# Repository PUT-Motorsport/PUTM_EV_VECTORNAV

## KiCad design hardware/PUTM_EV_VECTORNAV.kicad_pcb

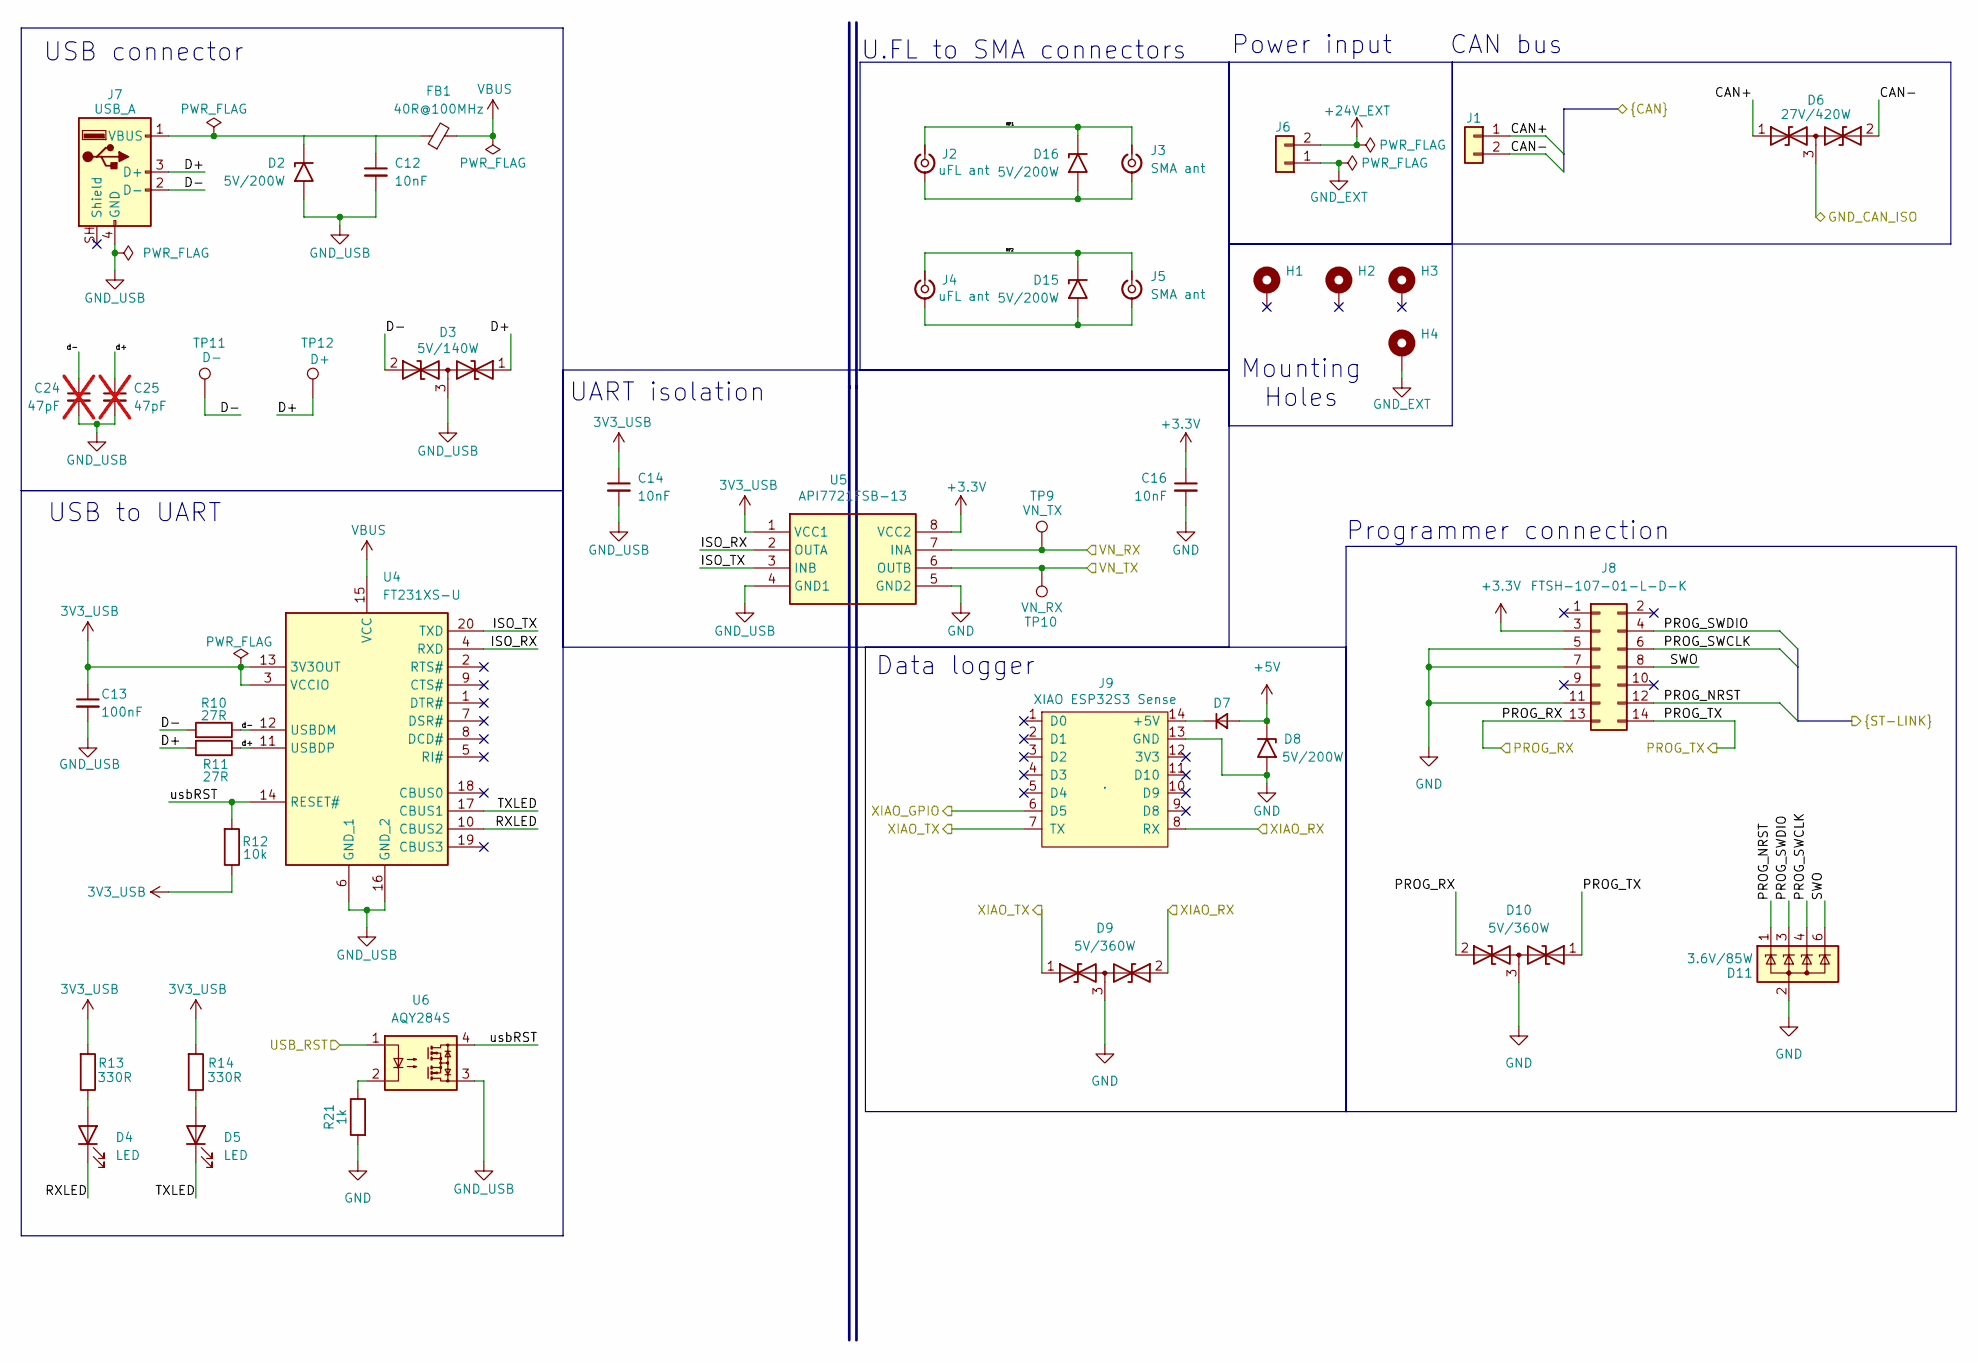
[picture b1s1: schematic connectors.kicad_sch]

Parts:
C12, C14, C16: 10nF; C_0603_1608Metric_Pad1.08x0.95mm_HandSolder
C13: 100nF; C_0603_1608Metric_Pad1.08x0.95mm_HandSolder; Mouser No 80-C0603C104M4RAUTO
C24, C25: 47pF; C_0603_1608Metric_Pad1.08x0.95mm_HandSolder; Mouser --; not fitted
D2, D8, D15, D16: 5V/200W; SODFL3618X110N
D3: 5V/140W; SOT-23-3
D4, D5: LED; D_0603_1608Metric_Pad1.05x0.95mm_HandSolder
D6: 27V/420W; SOT-23-3
D7: NSVRB751V40T1G; D_SOD-323_HandSoldering
D9, D10: 5V/360W; SOT-23_Handsoldering; Manufacturer_Part_Number STS232050B751; Mouser No 504-STS232050B751
D11: 3.6V/85W; SOT-23-6; Manufacturer_Part_Number ESDS304DBVR; Mouser No 595-ESDS304DBVR
FB1: 40R@100MHz; BEADC2012X110N
H1, H2, H3: MountingHole_Pad; MountingHole_3mm; Mouser ---
H4: MountingHole_Pad; MountingHole_3mm_Pad_Via; Mouser ---
J1, J6: Conn_01x02; StrainRelief; Manufacturer_Part_Number strain relief; Mouser ---
J2, J4: uFL ant; CONUFL001SMDT
J3, J5: SMA ant; SMACONNECTOR
J7: USB_A; UJ2AV4TH
J8: FTSH-107-01-L-D-K; FTSH-107-XX-YYY-D-K; Manufacturer_Part_Number FTSH-107-01-L-D-K; Mouser No 200-FTSH10701LDK
J9: XIAO ESP32S3 Sense; XIAO-ESP32S3-DIP; Mouser Part Number .
R10, R11: 27R; R_0603_1608Metric_Pad0.98x0.95mm_HandSolder
R12: 10k; R_0603_1608Metric_Pad0.98x0.95mm_HandSolder
R13, R14: 330R; R_0603_1608Metric_Pad0.98x0.95mm_HandSolder
R21: 1k; R_0603_1608Metric_Pad0.98x0.95mm_HandSolder
TP9: VN_TX; TestPoint_Pad_D1.0mm
TP10: VN_RX; TestPoint_Pad_D1.0mm
TP11: D-; TestPoint_Pad_D0.7mm
TP12: D+; TestPoint_Pad_D0.7mm
U4: FT231XS-U; SSOP-20_3.9x8.7mm_P0.635mm; Mouser Part Number 895-FT231XS-U
U5: API7721FSB-13; SOIC127P1150X280-8N
U6: AQY284S; SOP254P680X230-4N

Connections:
3V3_USB: C13.1, C14.1, R12.1, R13.2, R14.2, U4.3 (VCCIO), U4.13 (3V3OUT), U5.1 (VCC1)
+3.3V: C16.1, J8.3, U5.8 (VCC2); also elsewhere on the board
+5V: D7.2 (A), D8.1 (A1); also elsewhere on the board
+24V_EXT: J6.2; also elsewhere on the board
/CAN/CAN+: D6.1 (A1), J1.1; also elsewhere on the board
/CAN/CAN-: D6.2 (A2), J1.2; also elsewhere on the board
/CAN/GND_CAN_ISO: D6.3 (common); also elsewhere on the board
/Connectors/D+: D3.1 (A1), J7.3 (D+), R11.2, TP12.1 (1_1)
/Connectors/D-: D3.2 (A2), J7.2 (D-), R10.2, TP11.1 (1_1)
/Connectors/ISO_RX: U4.4 (RXD), U5.2 (OUTA)
/Connectors/ISO_TX: U4.20 (TXD), U5.3 (INB)
/Connectors/PROG_NRST: D11.1 (K), J8.12; also elsewhere on the board
/Connectors/PROG_RX: D10.2 (A2), J8.13; also elsewhere on the board
/Connectors/PROG_SWCLK: D11.4 (K), J8.6; also elsewhere on the board
/Connectors/PROG_SWDIO: D11.3 (K), J8.4; also elsewhere on the board
/Connectors/PROG_TX: D10.1 (A1), J8.14; also elsewhere on the board
/Connectors/RF1: D16.1 (A1), J2.1 (In), J3.1 (In)
/Connectors/RF2: D15.1 (A1), J4.1 (In), J5.1 (In)
/Connectors/RXLED: D4.1 (K), U4.10 (CBUS2)
/Connectors/SWO: D11.6 (K), J8.8
/Connectors/TXLED: D5.1 (K), U4.17 (CBUS1)
/Connectors/USB_RST: U6.1; also elsewhere on the board
/Connectors/VN_RX: TP9.1 (1_1), U5.7 (INA); also elsewhere on the board
/Connectors/VN_TX: TP10.1 (1_1), U5.6 (OUTB); also elsewhere on the board
/Connectors/XIAO_GPIO: J9.6 (D5); also elsewhere on the board
/Connectors/XIAO_RX: D9.2 (A2), J9.8 (RX); also elsewhere on the board
/Connectors/XIAO_TX: D9.1 (A1), J9.7 (TX); also elsewhere on the board
/Connectors/d+: C25.1, R11.1, U4.11 (USBDP)
/Connectors/d-: C24.1, R10.1, U4.12 (USBDM)
/Connectors/usbRST: R12.2, U4.14 (RESET#), U6.4
GND: C16.2, D8.2 (A2), D9.3 (common), D10.3 (common), D11.2 (A), D11.5 (K), J8.5, J8.7, J8.11, J9.13 (GND), R21.2, U5.5 (GND2); also elsewhere on the board
GND_EXT: H4.1 (1_1), J6.1; also elsewhere on the board
GND_USB: C12.2, C13.2, C14.2, C24.2, C25.2, D2.2 (A2), D3.3 (common), J7.4 (GND), U4.6 (GND_1), U4.16 (GND_2), U5.4 (GND1), U6.3
unnamed: C12.1, D2.1 (A1), FB1.1, J7.1 (VBUS)
unnamed: D4.2 (A), R13.1
unnamed: D5.2 (A), R14.1
unnamed: D7.1 (K), J9.14 (+5V)
unnamed: D15.2 (A2), J4.2 (Ext), J4.3 (Ext), J5.2 (Ext), J5.3 (Ext), J5.4 (Ext), J5.5 (Ext)
unnamed: D16.2 (A2), J2.2 (Ext), J2.3 (Ext), J3.2 (Ext), J3.3 (Ext), J3.4 (Ext), J3.5 (Ext)
unnamed: R21.1, U6.2
VBUS: FB1.2, U4.15 (VCC)

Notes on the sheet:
Power input
U.FL to SMA connectors
Data logger
UART isolation
USB connector
CAN bus
Mounting Holes
Programmer connection
USB to UART

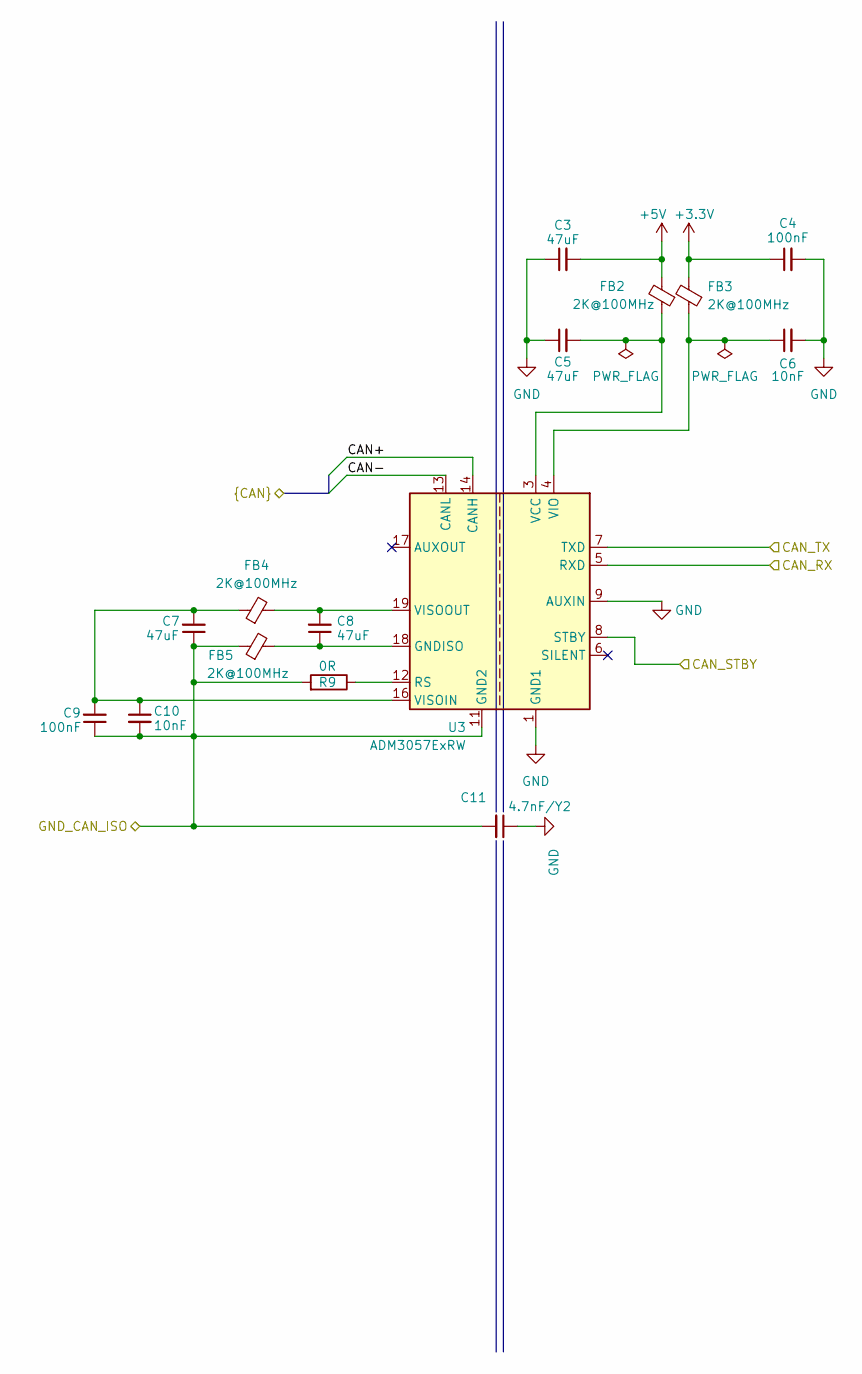
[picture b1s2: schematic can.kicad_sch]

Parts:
C3, C5, C7, C8: 47uF; C_0805_2012Metric_Pad1.18x1.45mm_HandSolder; Manufacturer_Part_Number GRM21BR61A476ME15L; Mouser No 81-GRM21BR61A476ME5L
C4, C9: 100nF; C_0603_1608Metric_Pad1.08x0.95mm_HandSolder; Manufacturer_Part_Number C0603C104M4RACAUTO; Mouser No 80-C0603C104M4RAUTO
C6, C10: 10nF; C_0603_1608Metric_Pad1.08x0.95mm_HandSolder; Manufacturer_Part_Number C0603C103J5RACAUTO; Mouser No 80-C0603C103J5RAUTO
C11: 4.7nF/Y2; CAPC5728X280N; Manufacturer_Part_Number S252B222K502CT; Mouser No 791-S252B222K502CT
FB2, FB3, FB4, FB5: 2K@100MHz; L_0805_2012Metric_Pad1.05x1.20mm_HandSolder; Manufacturer_Part_Number 2508052027Y1; Mouser No 623-2508052027Y1
R9: 0R; R_0603_1608Metric_Pad0.98x0.95mm_HandSolder
U3: ADM3057ExRW; SOIC-20W_7.5x12.8mm_P1.27mm; Manufacturer_Part_Number ADM3057EBRWZ; Mouser No 584-ADM3057EBRWZ

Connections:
+3.3V: C4.1, FB3.2; also elsewhere on the board
+5V: C3.2, FB2.2; also elsewhere on the board
/CAN/CAN+: U3.14 (CANH); also elsewhere on the board
/CAN/CAN-: U3.13 (CANL); also elsewhere on the board
/CAN/CAN_RX: U3.5 (RXD); also elsewhere on the board
/CAN/CAN_STBY: U3.8 (STBY); also elsewhere on the board
/CAN/CAN_TX: U3.7 (TXD); also elsewhere on the board
/CAN/GND_CAN_ISO: C7.1, C9.1, C10.2, C11.2, FB5.1, R9.2, U3.11 (GND2), U3.15 (GND2); also elsewhere on the board
GND: C3.1, C4.2, C5.1, C6.2, C11.1, U3.1 (GND1), U3.2 (GND1), U3.9 (AUXIN), U3.10 (GND1); also elsewhere on the board
unnamed: C8.1, FB5.2, U3.18 (GNDISO), U3.20 (GNDISO)
unnamed: R9.1, U3.12 (RS)
unnamed: C5.2, FB2.1, U3.3 (VCC)
unnamed: C6.1, FB3.1, U3.4 (VIO)
unnamed: C7.2, C9.2, C10.1, FB4.1, U3.16 (VISOIN)
unnamed: C8.2, FB4.2, U3.19 (VISOOUT)

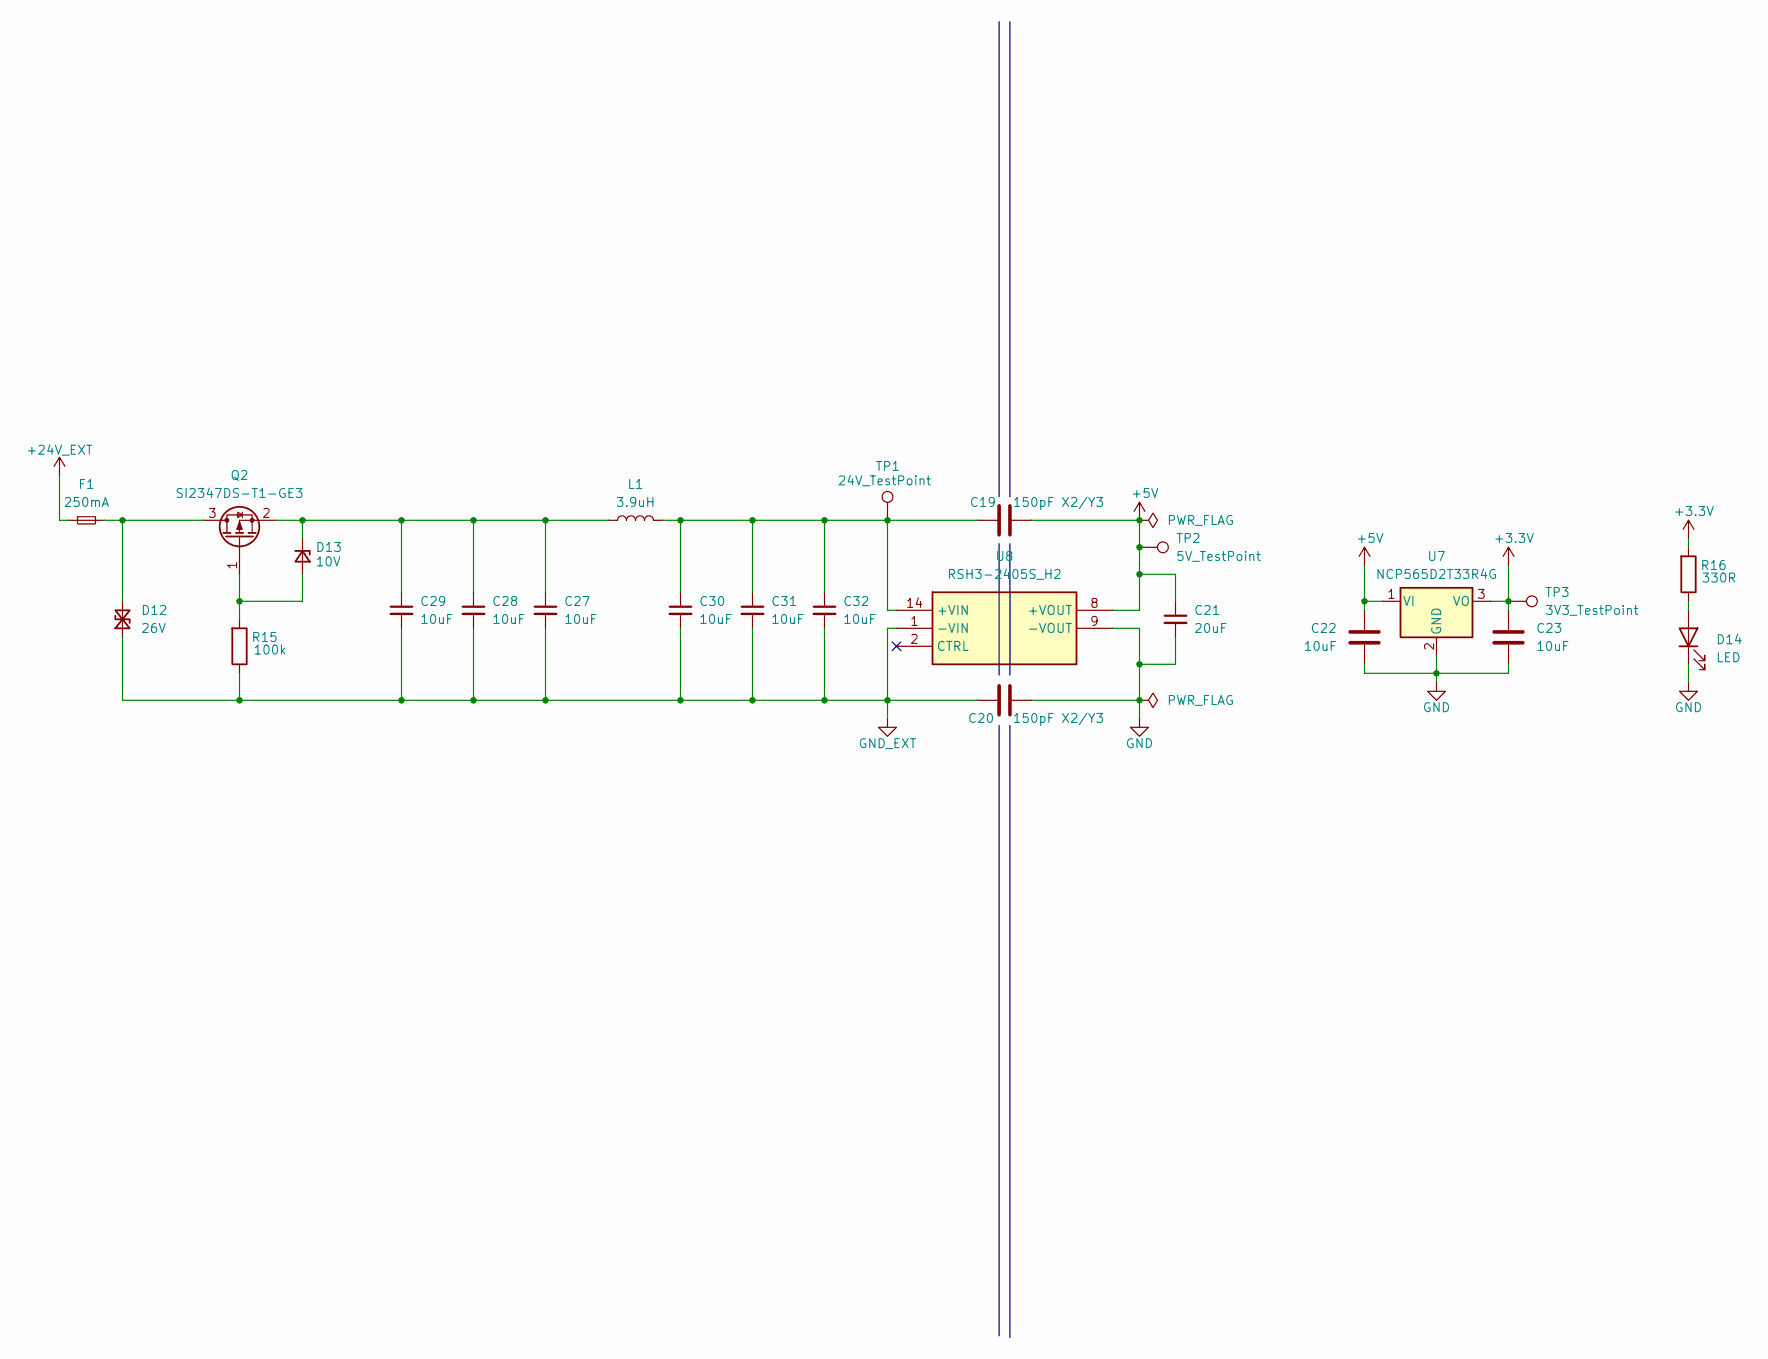
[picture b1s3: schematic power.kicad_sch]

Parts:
C19, C20: 150pF X2/Y3; CAPC4620X165N
C21: 20uF; GRM31x
C22, C23: 10uF; C_0603_1608Metric_Pad1.08x0.95mm_HandSolder
C27, C28, C29, C30, C31, C32: 10uF; C_1206_3216Metric
D12: 26V; SMFA2005CA
D13: 10V; SOD3716X135N
D14: LED; D_0603_1608Metric_Pad1.05x0.95mm_HandSolder
F1: 250mA; FUSC1608X43N
L1: 3.9uH; RLS397
Q2: SI2347DS-T1-GE3; SOT-23-3; Mouser Part Number 78-SI2347DS-T1-GE3
R15: 100k; R_0603_1608Metric_Pad0.98x0.95mm_HandSolder
R16: 330R; R_0603_1608Metric_Pad0.98x0.95mm_HandSolder
TP1: 24V_TestPoint; TestPoint_Pad_D1.0mm
TP2: 5V_TestPoint; TestPoint_Pad_D1.0mm
TP3: 3V3_TestPoint; TestPoint_Pad_D1.0mm
U7: NCP565D2T33R4G; TO-263-2
U8: RSH3-2405S_H2; RSH32405SH2; Mouser Part Number 919-RSH3-2405S/H2

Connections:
+3.3V: C23.2, R16.2, TP3.1 (1_1), U7.3 (VO); also elsewhere on the board
+5V: C19.2, C21.1, C22.2, TP2.1 (1_1), U7.1 (VI), U8.8 (+VOUT); also elsewhere on the board
+24V_EXT: F1.1; also elsewhere on the board
GND: C20.1, C21.2, C22.1, C23.1, D14.1 (K), U7.2 (GND), U8.9 (-VOUT); also elsewhere on the board
GND_EXT: C20.2, C27.2, C28.2, C29.2, C30.2, C31.2, C32.2, D12.1 (A1), R15.1, U8.1 (-VIN); also elsewhere on the board
unnamed: D12.2 (A2), F1.2, Q2.3 (D)
unnamed: D13.2 (A), Q2.1 (G), R15.2
unnamed: C27.1, C28.1, C29.1, D13.1 (K), L1.1, Q2.2 (S)
unnamed: D14.2 (A), R16.1
unnamed: C19.1, C30.1, C31.1, C32.1, L1.2, TP1.1 (1_1), U8.14 (+VIN)

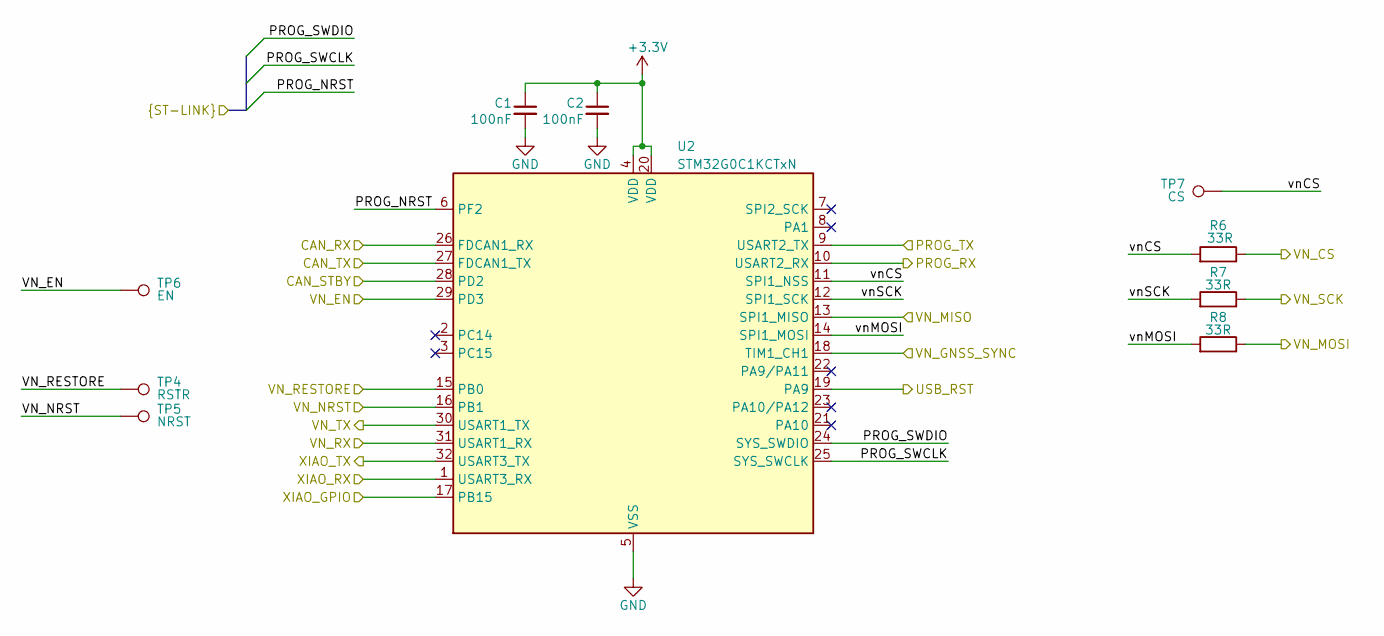
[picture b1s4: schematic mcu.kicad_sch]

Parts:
C1, C2: 100nF; C_0603_1608Metric_Pad1.08x0.95mm_HandSolder; Mouser No 80-C0603C104M4RAUTO
R6, R7, R8: 33R; R_0603_1608Metric_Pad0.98x0.95mm_HandSolder
TP4: RSTR; TestPoint_Pad_D1.0mm
TP5: NRST; TestPoint_Pad_D1.0mm
TP6: EN; TestPoint_Pad_D1.0mm
TP7: CS; TestPoint_Pad_D1.0mm
U2: STM32G0C1KCTxN; LQFP-32_7x7mm_P0.8mm

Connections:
+3.3V: C1.1, C2.1, U2.4 (VDD), U2.20 (VDD); also elsewhere on the board
/CAN/CAN_RX: U2.26 (FDCAN1_RX); also elsewhere on the board
/CAN/CAN_STBY: U2.28 (PD2); also elsewhere on the board
/CAN/CAN_TX: U2.27 (FDCAN1_TX); also elsewhere on the board
/Connectors/PROG_NRST: U2.6 (PF2); also elsewhere on the board
/Connectors/PROG_RX: U2.9 (USART2_TX); also elsewhere on the board
/Connectors/PROG_SWCLK: U2.25 (SYS_SWCLK); also elsewhere on the board
/Connectors/PROG_SWDIO: U2.24 (SYS_SWDIO); also elsewhere on the board
/Connectors/PROG_TX: U2.10 (USART2_RX); also elsewhere on the board
/Connectors/USB_RST: U2.19 (PA9); also elsewhere on the board
/Connectors/XIAO_GPIO: U2.17 (PB15); also elsewhere on the board
/Connectors/XIAO_RX: U2.32 (USART3_TX); also elsewhere on the board
/Connectors/XIAO_TX: U2.1 (USART3_RX); also elsewhere on the board
/MCU/VN_CS: R6.1; also elsewhere on the board
/MCU/VN_EN: TP6.1 (1_1), U2.29 (PD3); also elsewhere on the board
/MCU/VN_GNSS_SYNC: U2.18 (TIM1_CH1); also elsewhere on the board
/MCU/VN_MISO: U2.13 (SPI1_MISO); also elsewhere on the board
/MCU/VN_MOSI: R8.1; also elsewhere on the board
/MCU/VN_NRST: TP5.1 (1_1), U2.16 (PB1); also elsewhere on the board
/MCU/VN_RESTORE: TP4.1 (1_1), U2.15 (PB0); also elsewhere on the board
/MCU/VN_RX: U2.31 (USART1_RX); also elsewhere on the board
/MCU/VN_SCK: R7.1; also elsewhere on the board
/MCU/VN_TX: U2.30 (USART1_TX); also elsewhere on the board
/MCU/vnCS: R6.2, TP7.1 (1_1), U2.11 (SPI1_NSS)
/MCU/vnMOSI: R8.2, U2.14 (SPI1_MOSI)
/MCU/vnSCK: R7.2, U2.12 (SPI1_SCK)
GND: C1.2, C2.2, U2.5 (VSS); also elsewhere on the board

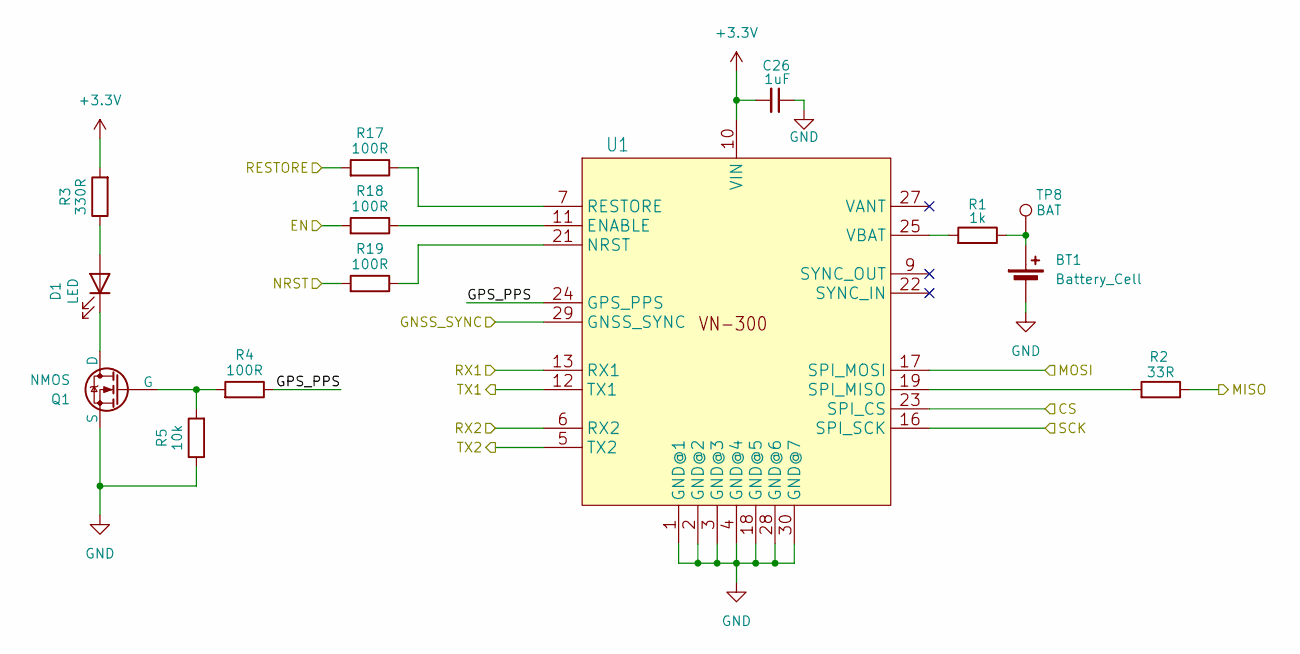
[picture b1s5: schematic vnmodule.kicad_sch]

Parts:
BT1: Battery_Cell; 2998TR
C26: 1uF; C_0603_1608Metric_Pad1.08x0.95mm_HandSolder; Manufacturer_Part_Number C0603C105K4RACTU; Mouser No 80-C0603C105K4R
D1: LED; D_0603_1608Metric_Pad1.05x0.95mm_HandSolder
Q1: NMOS; DMN63D8L13
R1: 1k; R_0603_1608Metric_Pad0.98x0.95mm_HandSolder
R2: 33R; R_0603_1608Metric_Pad0.98x0.95mm_HandSolder
R3: 330R; R_0603_1608Metric_Pad0.98x0.95mm_HandSolder
R4, R17, R18, R19: 100R; R_0603_1608Metric_Pad0.98x0.95mm_HandSolder
R5: 10k; R_0603_1608Metric_Pad0.98x0.95mm_HandSolder
TP8: BAT; TestPoint_Pad_D1.0mm
U1: VN-300; 7X8CASTLE; Mouser ---

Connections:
+3.3V: C26.2, R3.2, U1.10 (VIN); also elsewhere on the board
/Connectors/VN_RX: U1.12 (TX1); also elsewhere on the board
/Connectors/VN_TX: U1.13 (RX1); also elsewhere on the board
/MCU/VN_CS: U1.23 (SPI_CS); also elsewhere on the board
/MCU/VN_EN: R18.2; also elsewhere on the board
/MCU/VN_GNSS_SYNC: U1.29 (GNSS_SYNC); also elsewhere on the board
/MCU/VN_MISO: R2.1; also elsewhere on the board
/MCU/VN_MOSI: U1.17 (SPI_MOSI); also elsewhere on the board
/MCU/VN_NRST: R19.2; also elsewhere on the board
/MCU/VN_RESTORE: R17.2; also elsewhere on the board
/MCU/VN_RX: U1.5 (TX2); also elsewhere on the board
/MCU/VN_SCK: U1.16 (SPI_SCK); also elsewhere on the board
/MCU/VN_TX: U1.6 (RX2); also elsewhere on the board
/VectorNav/GPS_PPS: R4.1, U1.24 (GPS_PPS)
GND: BT1.2 (-), C26.1, Q1.3 (S), R5.1, U1.1 (GND@1), U1.2 (GND@2), U1.3 (GND@3), U1.4 (GND@4), U1.18 (GND@5), U1.28 (GND@6), U1.30 (GND@7); also elsewhere on the board
unnamed: BT1.1 (+), R1.1, TP8.1 (1_1)
unnamed: D1.2 (A), R3.1
unnamed: D1.1 (K), Q1.1 (D)
unnamed: Q1.2 (G), R4.2, R5.2
unnamed: R18.1, U1.11 (ENABLE)
unnamed: R19.1, U1.21 (NRST)
unnamed: R17.1, U1.7 (RESTORE)
unnamed: R2.2, U1.19 (SPI_MISO)
unnamed: R1.2, U1.25 (VBAT)

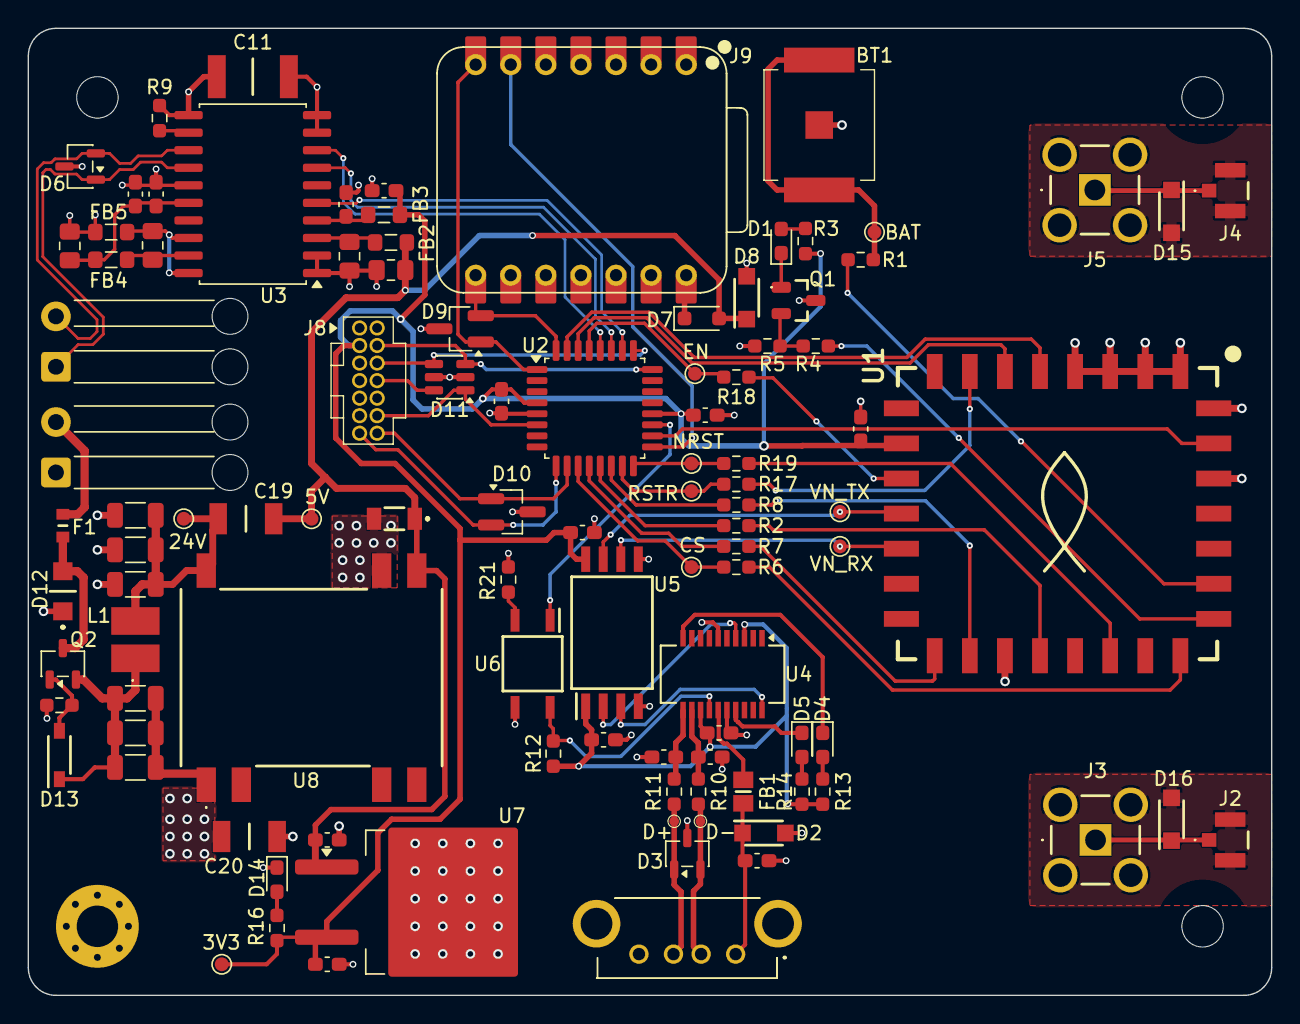
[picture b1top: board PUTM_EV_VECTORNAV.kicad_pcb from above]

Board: 4 copper layers, 90.0 x 70.0 mm, 108 parts (0 on the bottom side), 78 nets.

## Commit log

2026-04-11 Preliminary schematic
2026-04-23 Fixes after review
2026-04-27 Added pi-filter to VANT and added socket for battery
2026-05-04 Fixes after review and mouser links for most components added
2026-05-11 changed some elements on shematic
2026-05-11 mistake correction
2026-05-12 3D models, optocoupler added, pcb settings and components placing
2026-05-14 All components placed on pcb
2026-05-18 MCU and VN-300 routed
2026-05-19 Finished pcb routing
2026-06-02 Finished routing
2026-06-09 Some smaller fixes and final aesthetic changes
2026-06-23 little changes with traces and 3D models visibility
2026-06-30 Updated BOM
